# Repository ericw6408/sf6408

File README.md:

# SF6408

### Columnar staggered split keyboard based on the piantor: (https://github.com/beekeeb/piantor)

Made for HackClub's Blueprint program. Blueprint journal link here: https://blueprint.hackclub.com/projects/7322

if you can't view the image, paste the (kicad files) url into KiCanvas

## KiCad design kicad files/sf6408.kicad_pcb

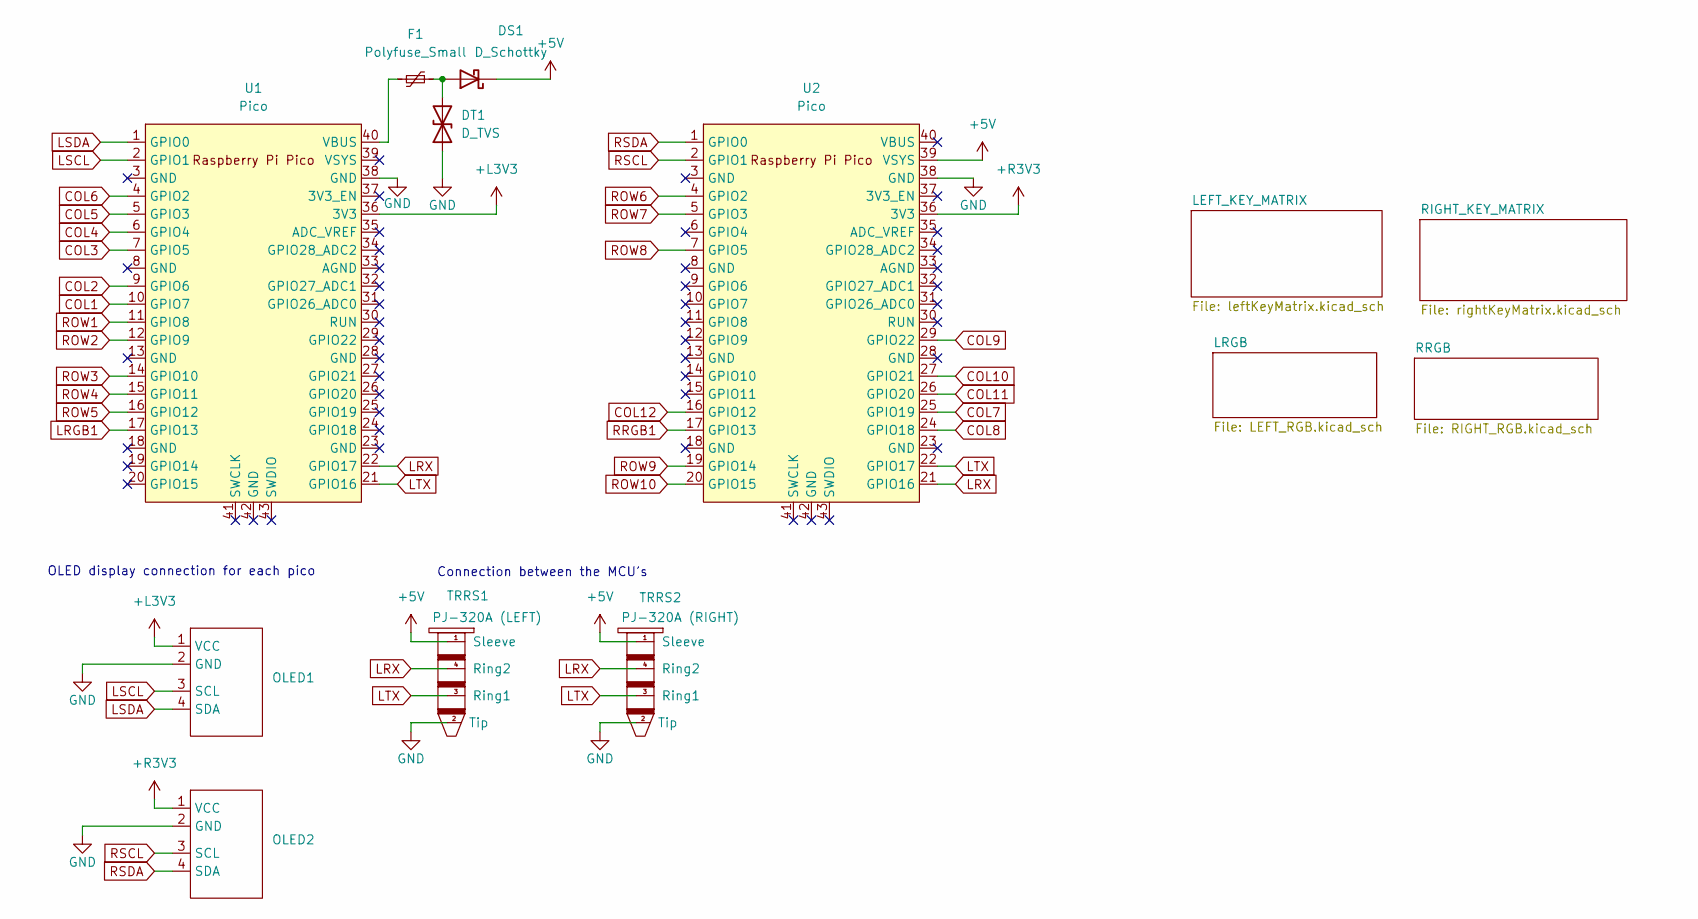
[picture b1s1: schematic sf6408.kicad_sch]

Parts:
DS1: D_Schottky; D_SMA
DT1: D_TVS; D_SMB
F1: Polyfuse_Small; Fuse_0402_1005Metric
OLED1, OLED2: OLED_CANADUINO
TRRS1: PJ-320A (LEFT); PJ-320A
TRRS2: PJ-320A (RIGHT); PJ-320A
U1, U2: Pico; RPi_Pico_SMD_TH

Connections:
+5V: DS1.1 (K), TRRS1.1 (Sleeve), TRRS2.1 (Sleeve), U2.39 (VSYS); also elsewhere on the board
+L3V3: OLED1.1 (VCC), U1.36 (3V3)
+R3V3: OLED2.1 (VCC), U2.36 (3V3)
COL1: U1.10 (GPIO7); also elsewhere on the board
COL2: U1.9 (GPIO6); also elsewhere on the board
COL3: U1.7 (GPIO5); also elsewhere on the board
COL4: U1.6 (GPIO4); also elsewhere on the board
COL5: U1.5 (GPIO3); also elsewhere on the board
COL6: U1.4 (GPIO2); also elsewhere on the board
COL7: U2.25 (GPIO19); also elsewhere on the board
COL8: U2.24 (GPIO18); also elsewhere on the board
COL9: U2.29 (GPIO22); also elsewhere on the board
COL10: U2.27 (GPIO21); also elsewhere on the board
COL11: U2.26 (GPIO20); also elsewhere on the board
COL12: U2.16 (GPIO12); also elsewhere on the board
GND: DT1.1 (A1), OLED1.2 (GND), OLED2.2 (GND), TRRS1.2 (Tip), TRRS2.2 (Tip), U1.38 (GND), U2.38 (GND); also elsewhere on the board
LRGB1: U1.17 (GPIO13); also elsewhere on the board
LRX: TRRS1.4 (Ring2), TRRS2.4 (Ring2), U1.22 (GPIO17), U2.21 (GPIO16)
LSCL: OLED1.3 (SCL), U1.2 (GPIO1)
LSDA: OLED1.4 (SDA), U1.1 (GPIO0)
LTX: TRRS1.3 (Ring1), TRRS2.3 (Ring1), U1.21 (GPIO16), U2.22 (GPIO17)
unnamed: DS1.2 (A), DT1.2 (A2), F1.1
unnamed: F1.2, U1.40 (VBUS)
ROW1: U1.11 (GPIO8); also elsewhere on the board
ROW2: U1.12 (GPIO9); also elsewhere on the board
ROW3: U1.14 (GPIO10); also elsewhere on the board
ROW4: U1.15 (GPIO11); also elsewhere on the board
ROW5: U1.16 (GPIO12); also elsewhere on the board
ROW6: U2.4 (GPIO2); also elsewhere on the board
ROW7: U2.5 (GPIO3); also elsewhere on the board
ROW8: U2.7 (GPIO5); also elsewhere on the board
ROW9: U2.19 (GPIO14); also elsewhere on the board
ROW10: U2.20 (GPIO15); also elsewhere on the board
RRGB1: U2.17 (GPIO13); also elsewhere on the board
RSCL: OLED2.3 (SCL), U2.2 (GPIO1)
RSDA: OLED2.4 (SDA), U2.1 (GPIO0)

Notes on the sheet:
Connection between the MCU's
OLED display connection for each pico

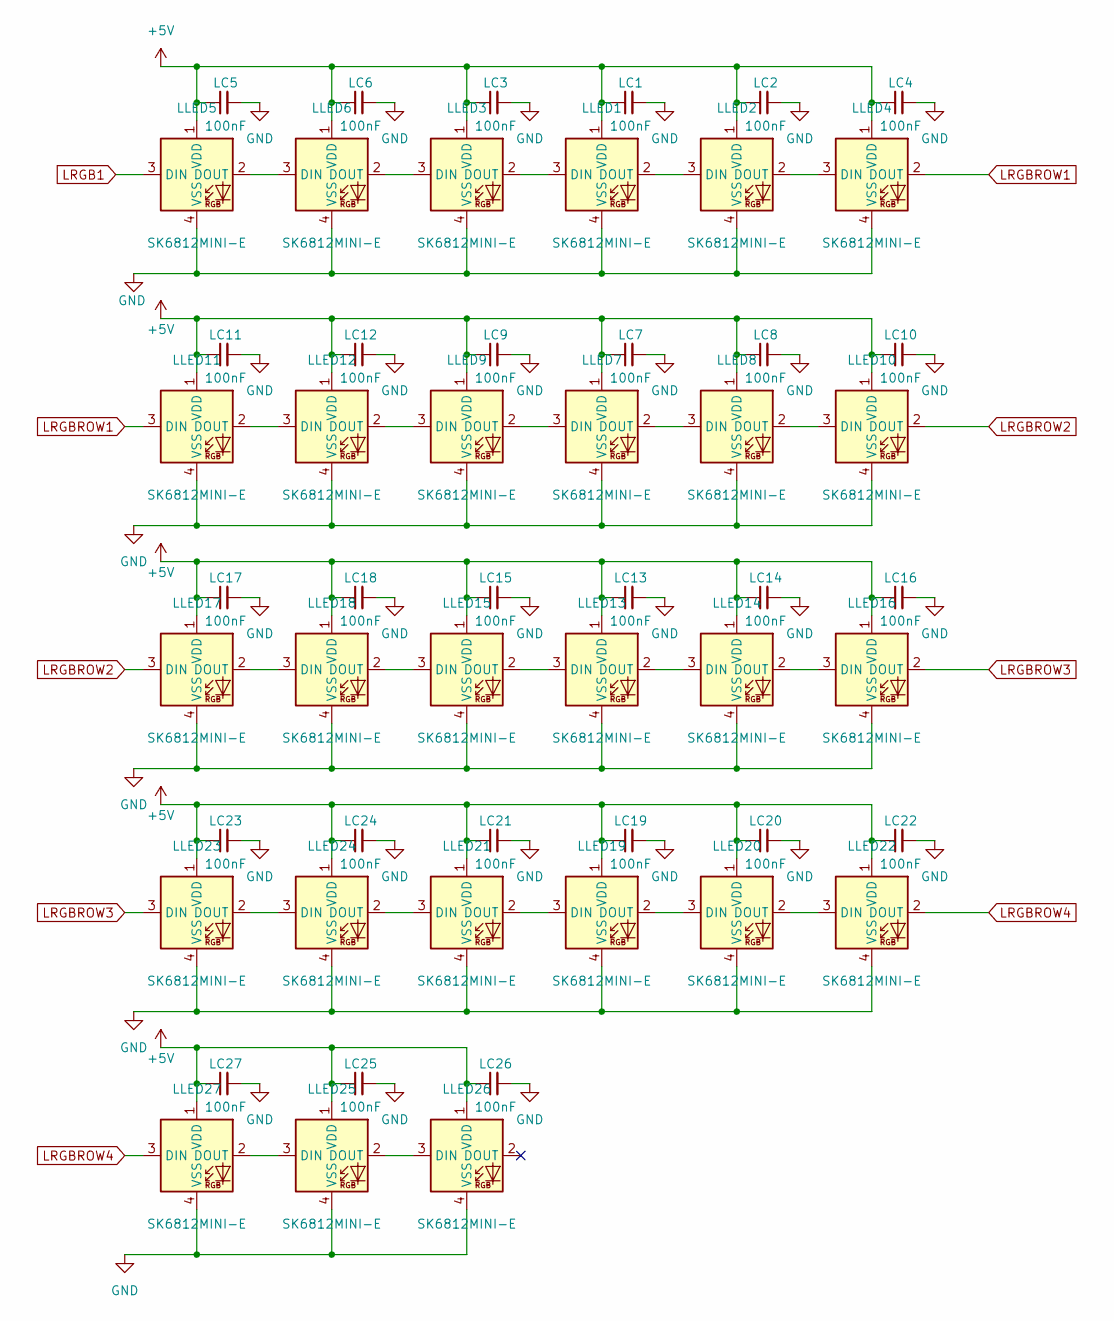
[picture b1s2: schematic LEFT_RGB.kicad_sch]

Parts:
LC1, LC2, LC3, LC4, LC5, LC6, LC7, LC8, LC9, LC10, LC11, LC12, LC13, LC14, LC15, LC16, LC17, LC18, LC19, LC20, LC21, LC22, LC23, LC24, LC25, LC26, LC27: 100nF; C_0402_1005Metric
LLED1, LLED2, LLED3, LLED4, LLED5, LLED6, LLED7, LLED8, LLED9, LLED10, LLED11, LLED12, LLED13, LLED14, LLED15, LLED16, LLED17, LLED18, LLED19, LLED20, LLED21, LLED22, LLED23, LLED24, LLED25, LLED26, LLED27: SK6812MINI-E; LED_6028R

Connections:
+5V: LC1.1, LC2.1, LC3.1, LC4.1, LC5.1, LC6.1, LC7.1, LC8.1, LC9.1, LC10.1, LC11.1, LC12.1, LC13.1, LC14.1, LC15.1, LC16.1, LC17.1, LC18.1, LC19.1, LC20.1, LC21.1, LC22.1, LC23.1, LC24.1, LC25.1, LC26.1, LC27.1, LLED1.1 (VDD), LLED2.1 (VDD), LLED3.1 (VDD), LLED4.1 (VDD), LLED5.1 (VDD), LLED6.1 (VDD), LLED7.1 (VDD), LLED8.1 (VDD), LLED9.1 (VDD), LLED10.1 (VDD), LLED11.1 (VDD), LLED12.1 (VDD), LLED13.1 (VDD), LLED14.1 (VDD), LLED15.1 (VDD), LLED16.1 (VDD), LLED17.1 (VDD), LLED18.1 (VDD), LLED19.1 (VDD), LLED20.1 (VDD), LLED21.1 (VDD), LLED22.1 (VDD), LLED23.1 (VDD), LLED24.1 (VDD), LLED25.1 (VDD), LLED26.1 (VDD), LLED27.1 (VDD); also elsewhere on the board
GND: LC1.2, LC2.2, LC3.2, LC4.2, LC5.2, LC6.2, LC7.2, LC8.2, LC9.2, LC10.2, LC11.2, LC12.2, LC13.2, LC14.2, LC15.2, LC16.2, LC17.2, LC18.2, LC19.2, LC20.2, LC21.2, LC22.2, LC23.2, LC24.2, LC25.2, LC26.2, LC27.2, LLED1.4 (VSS), LLED2.4 (VSS), LLED3.4 (VSS), LLED4.4 (VSS), LLED5.4 (VSS), LLED6.4 (VSS), LLED7.4 (VSS), LLED8.4 (VSS), LLED9.4 (VSS), LLED10.4 (VSS), LLED11.4 (VSS), LLED12.4 (VSS), LLED13.4 (VSS), LLED14.4 (VSS), LLED15.4 (VSS), LLED16.4 (VSS), LLED17.4 (VSS), LLED18.4 (VSS), LLED19.4 (VSS), LLED20.4 (VSS), LLED21.4 (VSS), LLED22.4 (VSS), LLED23.4 (VSS), LLED24.4 (VSS), LLED25.4 (VSS), LLED26.4 (VSS), LLED27.4 (VSS); also elsewhere on the board
LRGB1: LLED5.3 (DIN); also elsewhere on the board
LRGBROW1: LLED4.2 (DOUT), LLED11.3 (DIN)
LRGBROW2: LLED10.2 (DOUT), LLED17.3 (DIN)
LRGBROW3: LLED16.2 (DOUT), LLED23.3 (DIN)
LRGBROW4: LLED22.2 (DOUT), LLED27.3 (DIN)
unnamed: LLED1.3 (DIN), LLED3.2 (DOUT)
unnamed: LLED1.2 (DOUT), LLED2.3 (DIN)
unnamed: LLED2.2 (DOUT), LLED4.3 (DIN)
unnamed: LLED3.3 (DIN), LLED6.2 (DOUT)
unnamed: LLED5.2 (DOUT), LLED6.3 (DIN)
unnamed: LLED7.3 (DIN), LLED9.2 (DOUT)
unnamed: LLED7.2 (DOUT), LLED8.3 (DIN)
unnamed: LLED8.2 (DOUT), LLED10.3 (DIN)
unnamed: LLED11.2 (DOUT), LLED12.3 (DIN)
unnamed: LLED9.3 (DIN), LLED12.2 (DOUT)
unnamed: LLED13.3 (DIN), LLED15.2 (DOUT)
unnamed: LLED13.2 (DOUT), LLED14.3 (DIN)
unnamed: LLED14.2 (DOUT), LLED16.3 (DIN)
unnamed: LLED15.3 (DIN), LLED18.2 (DOUT)
unnamed: LLED17.2 (DOUT), LLED18.3 (DIN)
unnamed: LLED19.3 (DIN), LLED21.2 (DOUT)
unnamed: LLED19.2 (DOUT), LLED20.3 (DIN)
unnamed: LLED20.2 (DOUT), LLED22.3 (DIN)
unnamed: LLED21.3 (DIN), LLED24.2 (DOUT)
unnamed: LLED23.2 (DOUT), LLED24.3 (DIN)
unnamed: LLED25.3 (DIN), LLED27.2 (DOUT)
unnamed: LLED25.2 (DOUT), LLED26.3 (DIN)

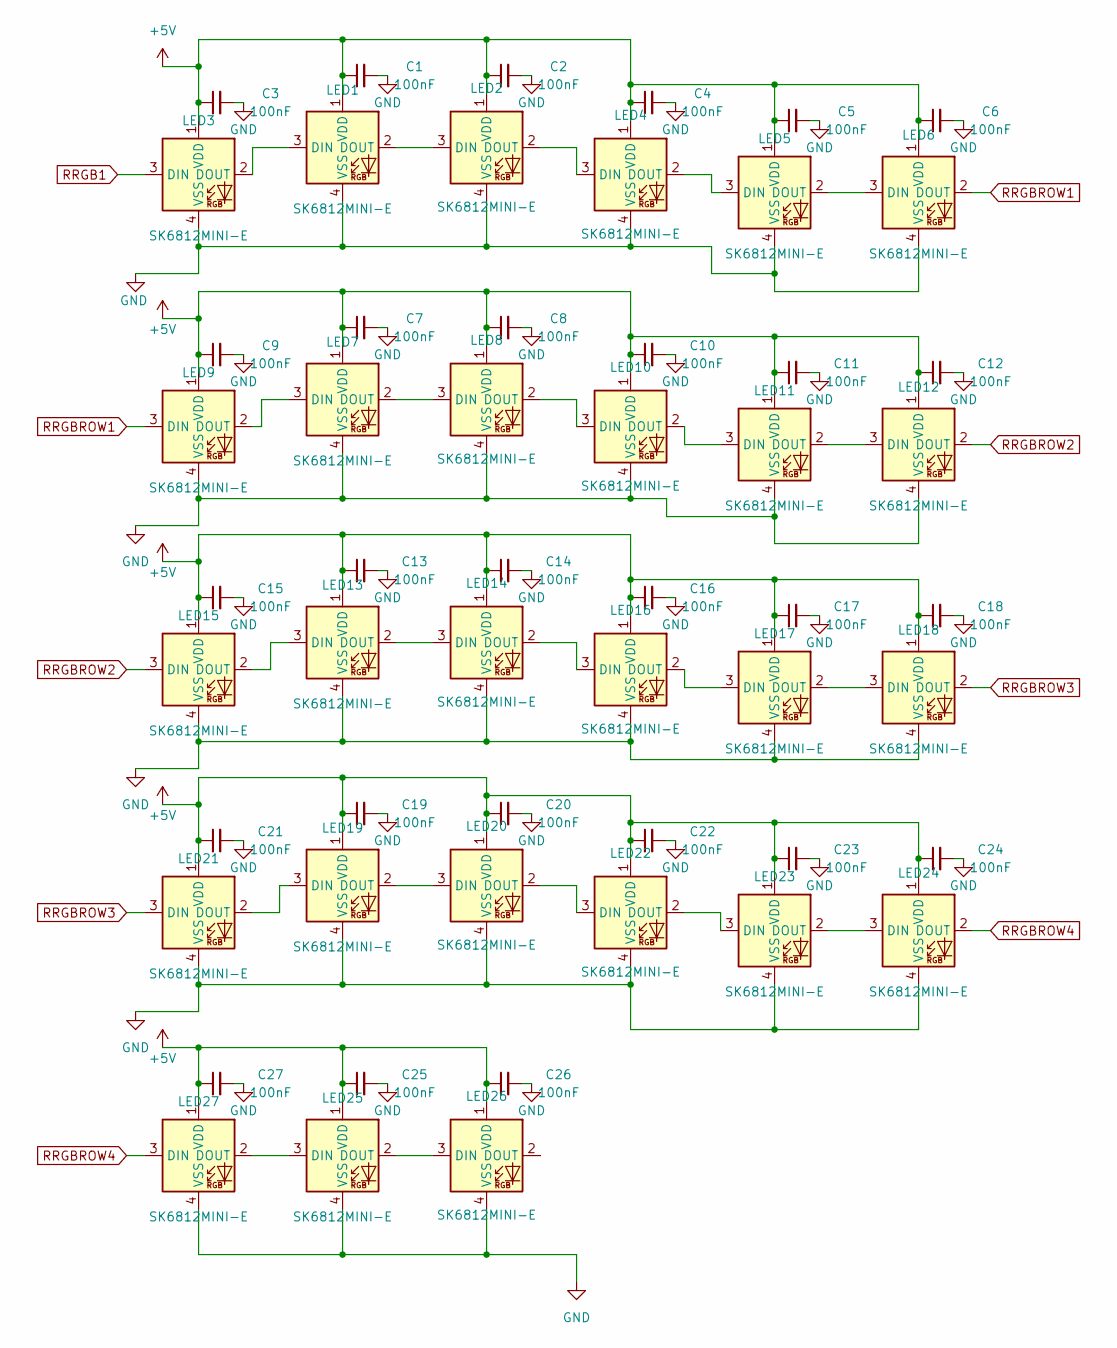
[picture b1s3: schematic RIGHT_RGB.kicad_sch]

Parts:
C1, C2, C3, C4, C5, C6, C7, C8, C9, C10, C11, C12, C13, C14, C15, C16, C17, C18, C19, C20, C21, C22, C23, C24, C25, C26, C27: 100nF; C_0402_1005Metric
LED1, LED2, LED3, LED4, LED5, LED6, LED7, LED8, LED9, LED10, LED11, LED12, LED13, LED14, LED15, LED16, LED17, LED18, LED19, LED20, LED21, LED22, LED23, LED24, LED25, LED26, LED27: SK6812MINI-E; LED_6028R

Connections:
+5V: C1.1, C2.1, C3.1, C4.1, C5.1, C6.1, C7.1, C8.1, C9.1, C10.1, C11.1, C12.1, C13.1, C14.1, C15.1, C16.1, C17.1, C18.1, C19.1, C20.1, C21.1, C22.1, C23.1, C24.1, C25.1, C26.1, C27.1, LED1.1 (VDD), LED2.1 (VDD), LED3.1 (VDD), LED4.1 (VDD), LED5.1 (VDD), LED6.1 (VDD), LED7.1 (VDD), LED8.1 (VDD), LED9.1 (VDD), LED10.1 (VDD), LED11.1 (VDD), LED12.1 (VDD), LED13.1 (VDD), LED14.1 (VDD), LED15.1 (VDD), LED16.1 (VDD), LED17.1 (VDD), LED18.1 (VDD), LED19.1 (VDD), LED20.1 (VDD), LED21.1 (VDD), LED22.1 (VDD), LED23.1 (VDD), LED24.1 (VDD), LED25.1 (VDD), LED26.1 (VDD), LED27.1 (VDD); also elsewhere on the board
GND: C1.2, C2.2, C3.2, C4.2, C5.2, C6.2, C7.2, C8.2, C9.2, C10.2, C11.2, C12.2, C13.2, C14.2, C15.2, C16.2, C17.2, C18.2, C19.2, C20.2, C21.2, C22.2, C23.2, C24.2, C25.2, C26.2, C27.2, LED1.4 (VSS), LED2.4 (VSS), LED3.4 (VSS), LED4.4 (VSS), LED5.4 (VSS), LED6.4 (VSS), LED7.4 (VSS), LED8.4 (VSS), LED9.4 (VSS), LED10.4 (VSS), LED11.4 (VSS), LED12.4 (VSS), LED13.4 (VSS), LED14.4 (VSS), LED15.4 (VSS), LED16.4 (VSS), LED17.4 (VSS), LED18.4 (VSS), LED19.4 (VSS), LED20.4 (VSS), LED21.4 (VSS), LED22.4 (VSS), LED23.4 (VSS), LED24.4 (VSS), LED25.4 (VSS), LED26.4 (VSS), LED27.4 (VSS); also elsewhere on the board
unnamed: LED1.3 (DIN), LED3.2 (DOUT)
unnamed: LED1.2 (DOUT), LED2.3 (DIN)
unnamed: LED2.2 (DOUT), LED4.3 (DIN)
unnamed: LED4.2 (DOUT), LED5.3 (DIN)
unnamed: LED5.2 (DOUT), LED6.3 (DIN)
unnamed: LED7.3 (DIN), LED9.2 (DOUT)
unnamed: LED7.2 (DOUT), LED8.3 (DIN)
unnamed: LED8.2 (DOUT), LED10.3 (DIN)
unnamed: LED10.2 (DOUT), LED11.3 (DIN)
unnamed: LED11.2 (DOUT), LED12.3 (DIN)
unnamed: LED13.3 (DIN), LED15.2 (DOUT)
unnamed: LED13.2 (DOUT), LED14.3 (DIN)
unnamed: LED14.2 (DOUT), LED16.3 (DIN)
unnamed: LED16.2 (DOUT), LED17.3 (DIN)
unnamed: LED17.2 (DOUT), LED18.3 (DIN)
unnamed: LED19.3 (DIN), LED21.2 (DOUT)
unnamed: LED19.2 (DOUT), LED20.3 (DIN)
unnamed: LED20.2 (DOUT), LED22.3 (DIN)
unnamed: LED22.2 (DOUT), LED23.3 (DIN)
unnamed: LED23.2 (DOUT), LED24.3 (DIN)
unnamed: LED25.3 (DIN), LED27.2 (DOUT)
unnamed: LED25.2 (DOUT), LED26.3 (DIN)
RRGB1: LED3.3 (DIN); also elsewhere on the board
RRGBROW1: LED6.2 (DOUT), LED9.3 (DIN)
RRGBROW2: LED12.2 (DOUT), LED15.3 (DIN)
RRGBROW3: LED18.2 (DOUT), LED21.3 (DIN)
RRGBROW4: LED24.2 (DOUT), LED27.3 (DIN)

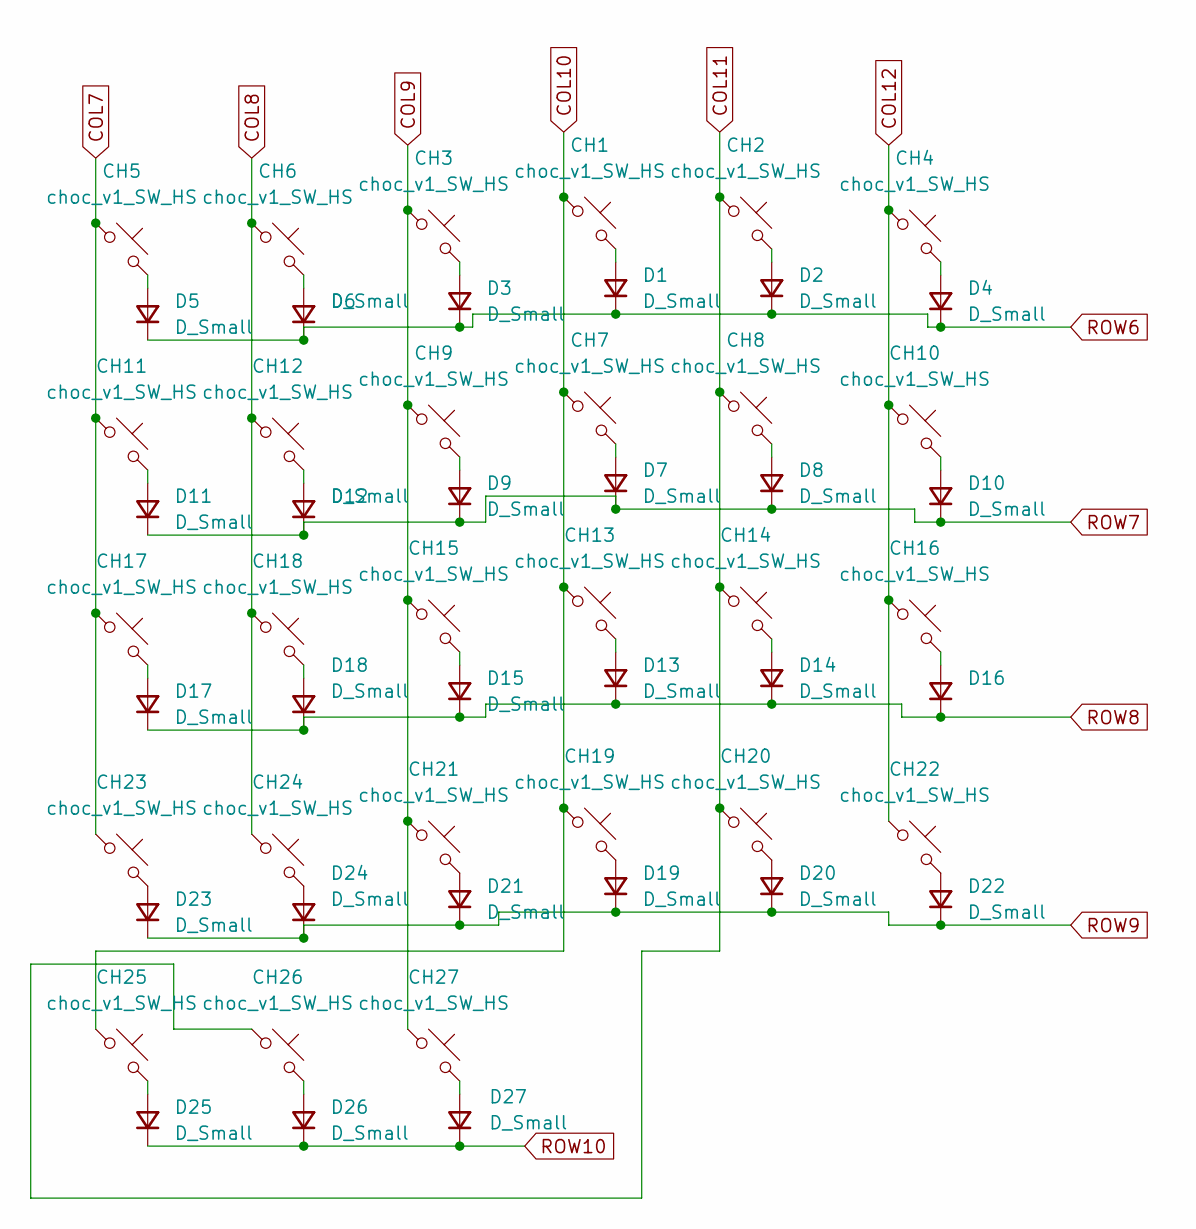
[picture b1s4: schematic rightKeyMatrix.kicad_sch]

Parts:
CH1, CH2, CH3, CH4, CH5, CH6, CH7, CH8, CH9, CH10, CH11, CH12, CH13, CH14, CH15, CH16, CH17, CH18, CH19, CH20, CH21, CH22, CH23, CH24, CH25, CH26, CH27: choc_v1_SW_HS; SW_choc_v1_HS_CPG135001S30_1u
D1, D2, D3, D4, D5, D6, D7, D8, D9, D10, D11, D12, D13, D14, D15, D16, D17, D18, D19, D20, D21, D22, D23, D24, D25, D26, D27: D_Small; D_SOD-323

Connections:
COL7: CH5.1, CH11.1, CH17.1, CH23.1; also elsewhere on the board
COL8: CH6.1, CH12.1, CH18.1, CH24.1; also elsewhere on the board
COL9: CH3.1, CH9.1, CH15.1, CH21.1, CH27.1; also elsewhere on the board
COL10: CH1.1, CH7.1, CH13.1, CH19.1, CH25.1; also elsewhere on the board
COL11: CH2.1, CH8.1, CH14.1, CH20.1, CH26.1; also elsewhere on the board
COL12: CH4.1, CH10.1, CH16.1, CH22.1; also elsewhere on the board
unnamed: CH1.2, D1.2 (A)
unnamed: CH2.2, D2.2 (A)
unnamed: CH3.2, D3.2 (A)
unnamed: CH4.2, D4.2 (A)
unnamed: CH5.2, D5.2 (A)
unnamed: CH6.2, D6.2 (A)
unnamed: CH7.2, D7.2 (A)
unnamed: CH8.2, D8.2 (A)
unnamed: CH9.2, D9.2 (A)
unnamed: CH10.2, D10.2 (A)
unnamed: CH11.2, D11.2 (A)
unnamed: CH12.2, D12.2 (A)
unnamed: CH13.2, D13.2 (A)
unnamed: CH14.2, D14.2 (A)
unnamed: CH15.2, D15.2 (A)
unnamed: CH16.2, D16.2 (A)
unnamed: CH17.2, D17.2 (A)
unnamed: CH18.2, D18.2 (A)
unnamed: CH19.2, D19.2 (A)
unnamed: CH20.2, D20.2 (A)
unnamed: CH21.2, D21.2 (A)
unnamed: CH22.2, D22.2 (A)
unnamed: CH23.2, D23.2 (A)
unnamed: CH24.2, D24.2 (A)
unnamed: CH25.2, D25.2 (A)
unnamed: CH26.2, D26.2 (A)
unnamed: CH27.2, D27.2 (A)
ROW6: D1.1 (K), D2.1 (K), D3.1 (K), D4.1 (K), D5.1 (K), D6.1 (K); also elsewhere on the board
ROW7: D7.1 (K), D8.1 (K), D9.1 (K), D10.1 (K), D11.1 (K), D12.1 (K); also elsewhere on the board
ROW8: D13.1 (K), D14.1 (K), D15.1 (K), D16.1 (K), D17.1 (K), D18.1 (K); also elsewhere on the board
ROW9: D19.1 (K), D20.1 (K), D21.1 (K), D22.1 (K), D23.1 (K), D24.1 (K); also elsewhere on the board
ROW10: D25.1 (K), D26.1 (K), D27.1 (K); also elsewhere on the board

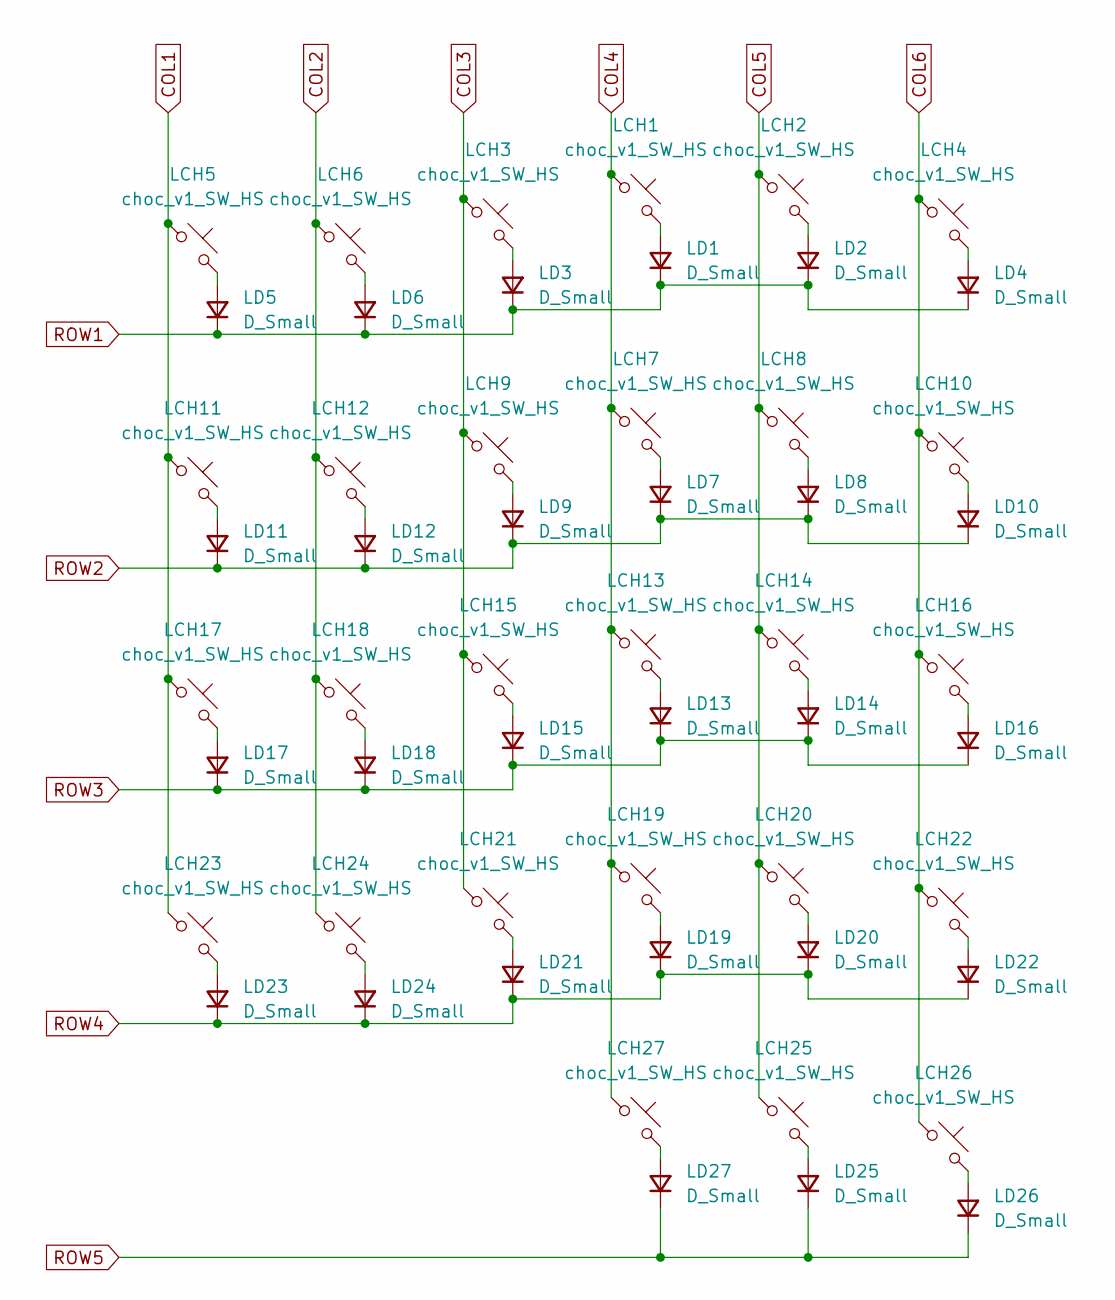
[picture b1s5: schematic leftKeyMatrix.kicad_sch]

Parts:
LCH1, LCH2, LCH3, LCH4, LCH5, LCH6, LCH7, LCH8, LCH9, LCH10, LCH11, LCH12, LCH13, LCH14, LCH15, LCH16, LCH17, LCH18, LCH19, LCH20, LCH21, LCH22, LCH23, LCH24, LCH25, LCH26, LCH27: choc_v1_SW_HS; SW_choc_v1_HS_CPG135001S30_1u
LD1, LD2, LD3, LD4, LD5, LD6, LD7, LD8, LD9, LD10, LD11, LD12, LD13, LD14, LD15, LD16, LD17, LD18, LD19, LD20, LD21, LD22, LD23, LD24, LD25, LD26, LD27: D_Small; D_SOD-323

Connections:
COL1: LCH5.1, LCH11.1, LCH17.1, LCH23.1; also elsewhere on the board
COL2: LCH6.1, LCH12.1, LCH18.1, LCH24.1; also elsewhere on the board
COL3: LCH3.1, LCH9.1, LCH15.1, LCH21.1; also elsewhere on the board
COL4: LCH1.1, LCH7.1, LCH13.1, LCH19.1, LCH27.1; also elsewhere on the board
COL5: LCH2.1, LCH8.1, LCH14.1, LCH20.1, LCH25.1; also elsewhere on the board
COL6: LCH4.1, LCH10.1, LCH16.1, LCH22.1, LCH26.1; also elsewhere on the board
unnamed: LCH1.2, LD1.2 (A)
unnamed: LCH2.2, LD2.2 (A)
unnamed: LCH3.2, LD3.2 (A)
unnamed: LCH4.2, LD4.2 (A)
unnamed: LCH5.2, LD5.2 (A)
unnamed: LCH6.2, LD6.2 (A)
unnamed: LCH7.2, LD7.2 (A)
unnamed: LCH8.2, LD8.2 (A)
unnamed: LCH9.2, LD9.2 (A)
unnamed: LCH10.2, LD10.2 (A)
unnamed: LCH11.2, LD11.2 (A)
unnamed: LCH12.2, LD12.2 (A)
unnamed: LCH13.2, LD13.2 (A)
unnamed: LCH14.2, LD14.2 (A)
unnamed: LCH15.2, LD15.2 (A)
unnamed: LCH16.2, LD16.2 (A)
unnamed: LCH17.2, LD17.2 (A)
unnamed: LCH18.2, LD18.2 (A)
unnamed: LCH19.2, LD19.2 (A)
unnamed: LCH20.2, LD20.2 (A)
unnamed: LCH21.2, LD21.2 (A)
unnamed: LCH22.2, LD22.2 (A)
unnamed: LCH23.2, LD23.2 (A)
unnamed: LCH24.2, LD24.2 (A)
unnamed: LCH25.2, LD25.2 (A)
unnamed: LCH26.2, LD26.2 (A)
unnamed: LCH27.2, LD27.2 (A)
ROW1: LD1.1 (K), LD2.1 (K), LD3.1 (K), LD4.1 (K), LD5.1 (K), LD6.1 (K); also elsewhere on the board
ROW2: LD7.1 (K), LD8.1 (K), LD9.1 (K), LD10.1 (K), LD11.1 (K), LD12.1 (K); also elsewhere on the board
ROW3: LD13.1 (K), LD14.1 (K), LD15.1 (K), LD16.1 (K), LD17.1 (K), LD18.1 (K); also elsewhere on the board
ROW4: LD19.1 (K), LD20.1 (K), LD21.1 (K), LD22.1 (K), LD23.1 (K), LD24.1 (K); also elsewhere on the board
ROW5: LD25.1 (K), LD26.1 (K), LD27.1 (K); also elsewhere on the board

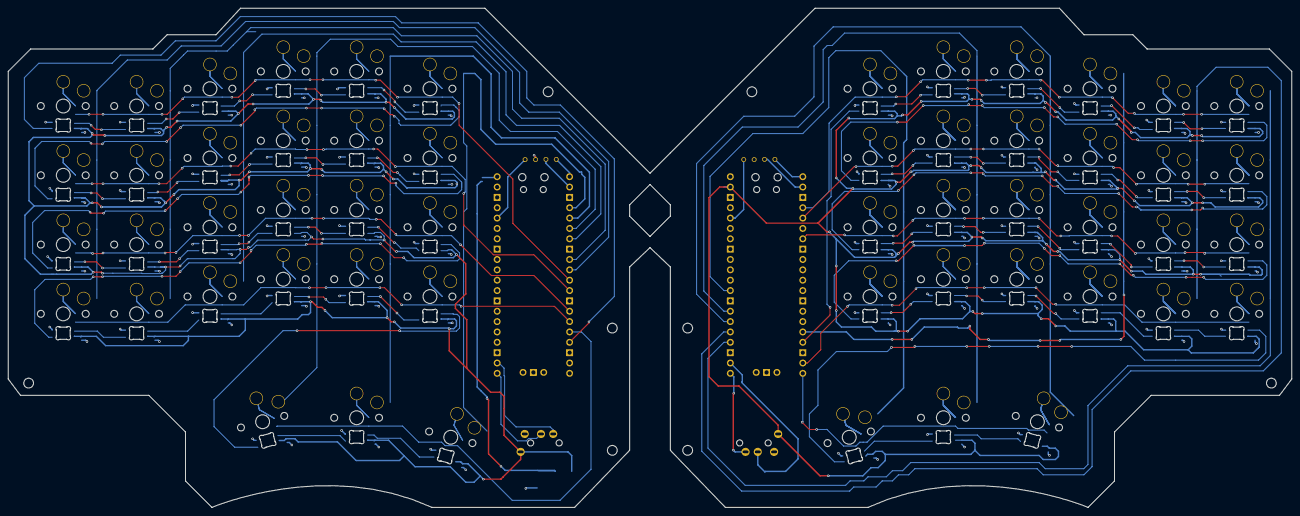
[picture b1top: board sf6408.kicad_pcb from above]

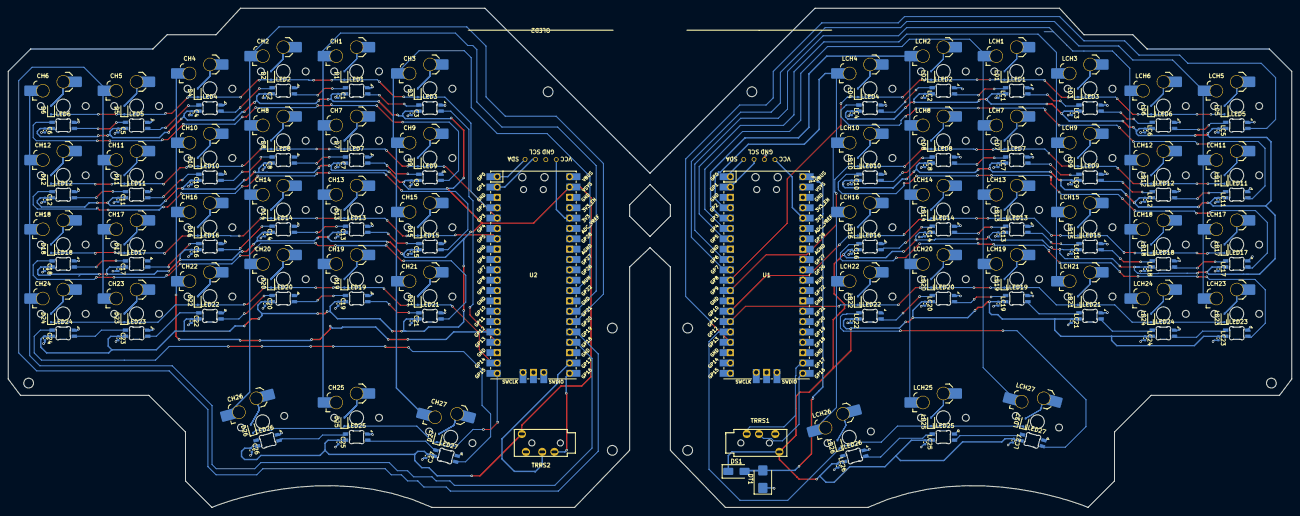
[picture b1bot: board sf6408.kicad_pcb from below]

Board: 2 copper layers, 314.9 x 122.4 mm, 225 parts (225 on the bottom side), 142 nets.

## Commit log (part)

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2025-12-28 KiCad files
    PCB & schematic
2025-12-28 Readme
